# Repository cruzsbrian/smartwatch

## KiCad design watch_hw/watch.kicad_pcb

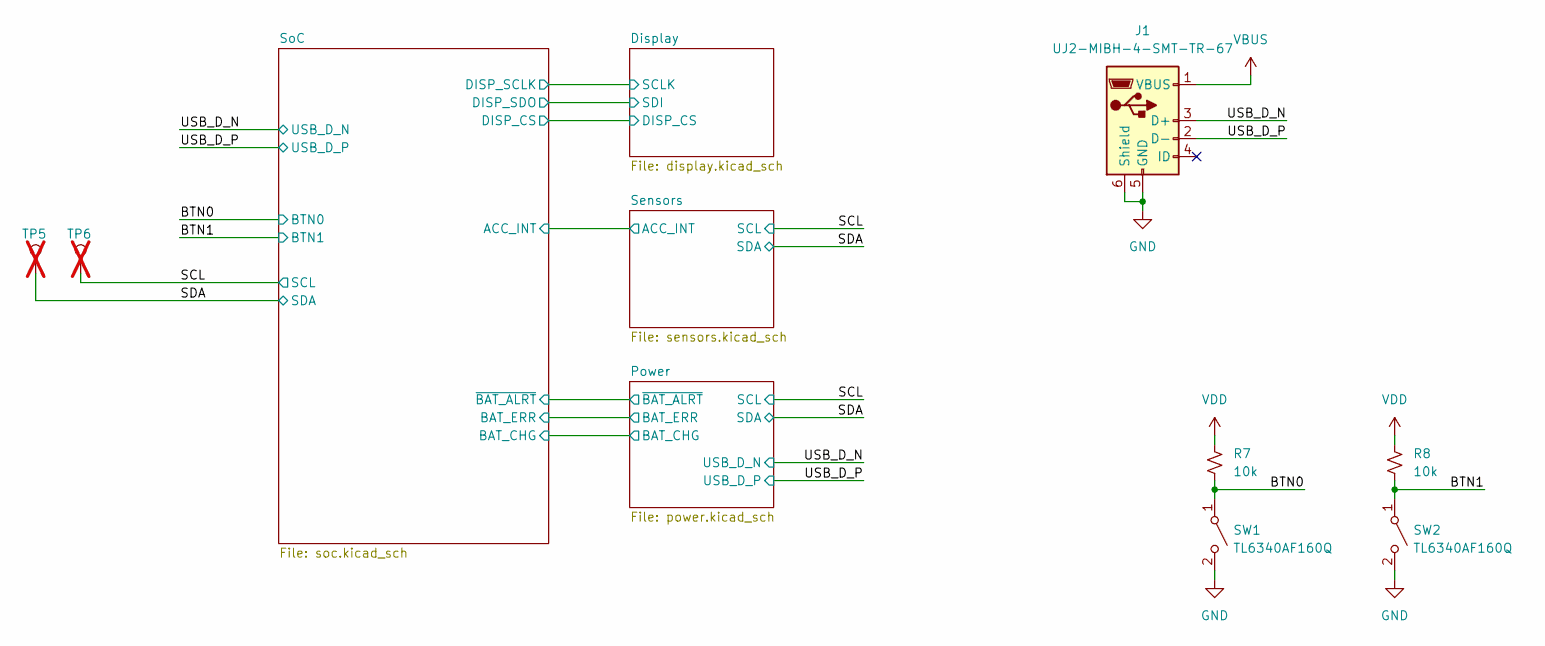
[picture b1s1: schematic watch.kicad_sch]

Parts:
J1: UJ2-MIBH-4-SMT-TR-67; Manufacturer Part Number UJ2-MIBH-4-SMT-TR-67; LCSC C22359766
R7, R8: 10k; R_0402_1005Metric_Pad0.72x0.64mm_HandSolder; Manufacturer Part Number 0402WGF1002TCE; LCSC C25744
SW1, SW2: TL6340AF160Q; SW_TL6340AF160Q; Manufacturer Part Number TL6340AF160Q; LCSC C4944967
TP5, TP6: TestPoint; TestPoint_Keystone_5015_Micro_Mini; not fitted

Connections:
/BTN0: R7.2, SW1.1 (A); also elsewhere on the board
/BTN1: R8.2, SW2.1 (A); also elsewhere on the board
/SCL: TP6.1; also elsewhere on the board
/SDA: TP5.1; also elsewhere on the board
/USB_D_N: J1.3 (D+); also elsewhere on the board
/USB_D_P: J1.2 (D-); also elsewhere on the board
GND: J1.5 (GND), J1.6 (Shield), SW1.2 (B), SW2.2 (B); also elsewhere on the board
VBUS: J1.1 (VBUS); also elsewhere on the board
VDD: R7.1, R8.1; also elsewhere on the board

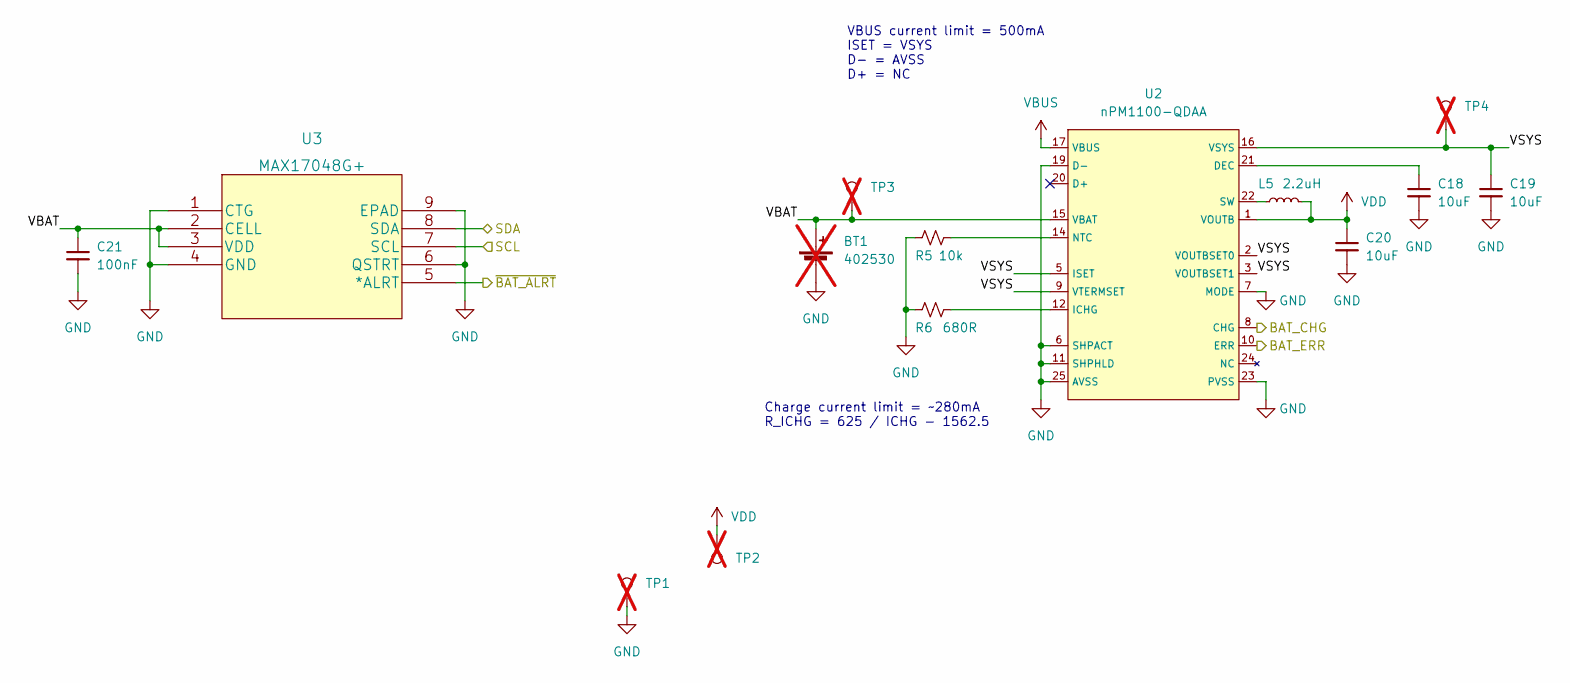
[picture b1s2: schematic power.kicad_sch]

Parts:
BT1: 402530; PinHeader_1x02_P1.27mm_Vertical; not fitted
C18, C19, C20: 10uF; C_0805_2012Metric_Pad1.18x1.45mm_HandSolder; Manufacturer Part Number CL21A106KAYNNNE; LCSC C15850
C21: 100nF; C_0402_1005Metric_Pad0.74x0.62mm_HandSolder; Manufacturer Part Number CL05B104KO5NNNC; LCSC C1525
L5: 2.2uH; L_0805_2012Metric_Pad1.05x1.20mm_HandSolder; Manufacturer Part Number LQM21PN2R2MGHL; LCSC C341781
R5: 10k; R_0402_1005Metric_Pad0.72x0.64mm_HandSolder; Manufacturer Part Number 0402WGF1002TCE; LCSC C25744
R6: 680R; R_0402_1005Metric_Pad0.72x0.64mm_HandSolder; Manufacturer Part Number 0402WGF6800TCE; LCSC C25130
TP1, TP2, TP3, TP4: TestPoint; TestPoint_Keystone_5015_Micro_Mini; not fitted
U2: nPM1100-QDAA; QFN-24-1EP_4x4mm_P0.5mm_EP2.15x2.15mm; Manufacturer Part Number NPM1100-QDAA-R; LCSC C5816773
U3: MAX17048G+; MAX17048G&plus_; Manufacturer Part Number MAX17048G+T10; LCSC C2682616

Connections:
/Power/BAT_CHG: U2.8 (CHG); also elsewhere on the board
/Power/BAT_ERR: U2.10 (ERR); also elsewhere on the board
/Power/VBAT: BT1.1 (+), C21.1, TP3.1, U2.15 (VBAT), U3.2 (CELL), U3.3 (VDD)
/Power/VSYS: C19.1, TP4.1, U2.2 (VOUTBSET0), U2.3 (VOUTBSET1), U2.5 (ISET), U2.9 (VTERMSET), U2.16 (VSYS)
/Power/~BAT_ALRT: U3.5 (*ALRT); also elsewhere on the board
/SCL: U3.7 (SCL); also elsewhere on the board
/SDA: U3.8 (SDA); also elsewhere on the board
GND: BT1.2 (-), C18.2, C19.2, C20.2, C21.2, R5.1, R6.1, TP1.1, U2.6 (SHPACT), U2.7 (MODE), U2.11 (SHPHLD), U2.19 (D-), U2.23 (PVSS), U2.25 (AVSS), U3.1 (CTG), U3.4 (GND), U3.6 (QSTRT), U3.9 (EPAD); also elsewhere on the board
unnamed: C18.1, U2.21 (DEC)
unnamed: R6.2, U2.12 (ICHG)
unnamed: R5.2, U2.14 (NTC)
unnamed: L5.1, U2.22 (SW)
VBUS: U2.17 (VBUS); also elsewhere on the board
VDD: C20.1, L5.2, TP2.1, U2.1 (VOUTB); also elsewhere on the board

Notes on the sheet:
Charge current limit = ~280mA R_ICHG = 625 / ICHG - 1562.5
VBUS current limit = 500mA ISET = VSYS D- = AVSS D+ = NC

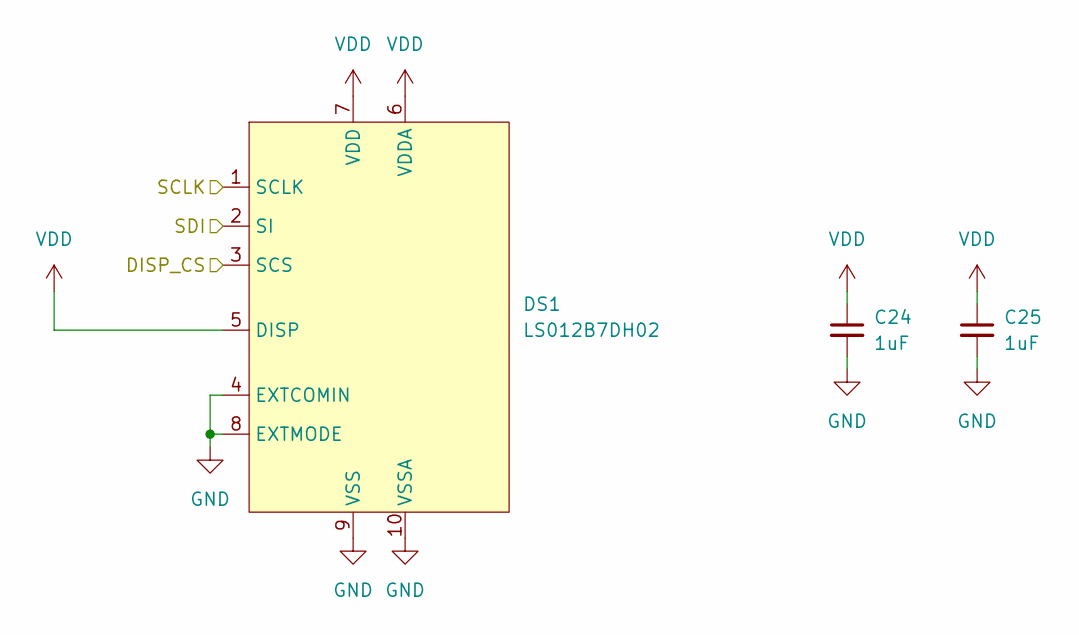
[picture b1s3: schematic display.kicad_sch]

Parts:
C24, C25: 1uF; C_0402_1005Metric_Pad0.74x0.62mm_HandSolder; Manufacturer Part Number CL05A105KA5NQNC; LCSC C52923
DS1: LS012B7DH02; AYF531035A; Manufacturer Part Number AYF531035A

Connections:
/Display/DISP_CS: DS1.3 (SCS); also elsewhere on the board
/Display/SCLK: DS1.1 (SCLK); also elsewhere on the board
/Display/SDI: DS1.2 (SI); also elsewhere on the board
GND: C24.2, C25.2, DS1.4 (EXTCOMIN), DS1.8 (EXTMODE), DS1.9 (VSS), DS1.10 (VSSA); also elsewhere on the board
VDD: C24.1, C25.1, DS1.5 (DISP), DS1.6 (VDDA), DS1.7 (VDD); also elsewhere on the board

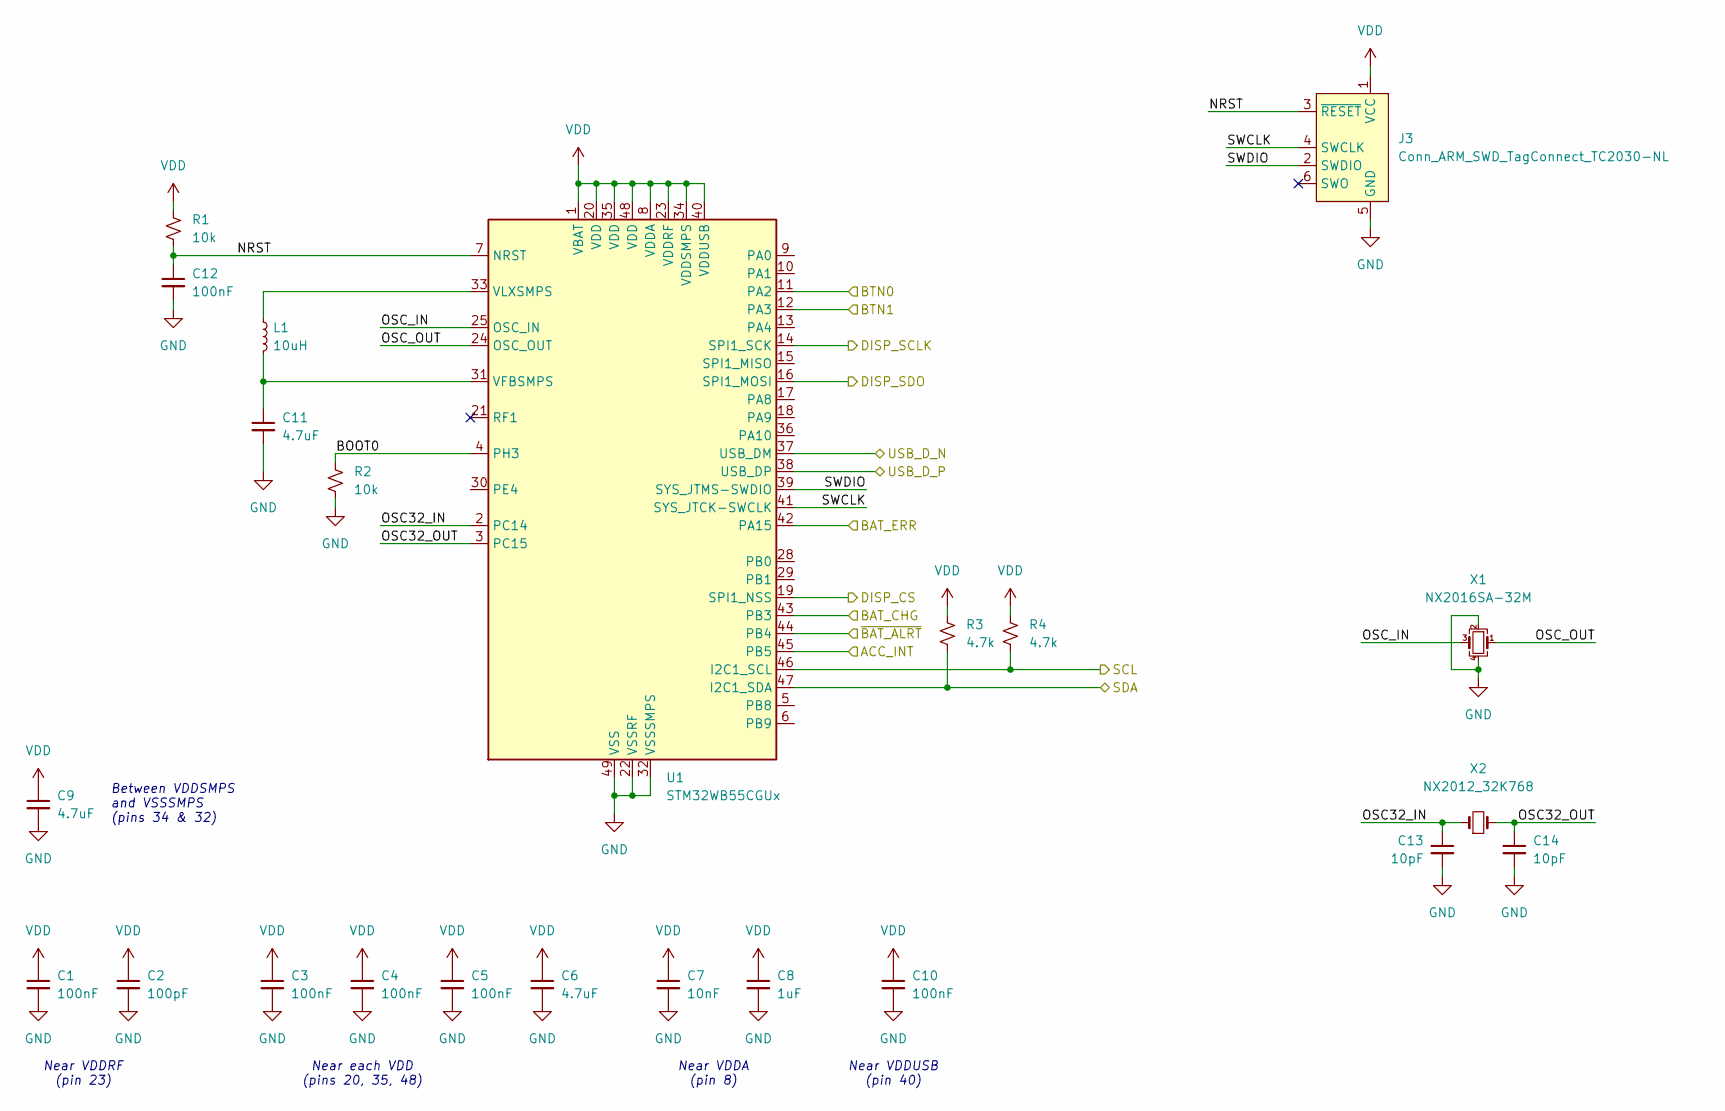
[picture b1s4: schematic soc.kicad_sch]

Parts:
C1, C3, C4, C5, C10, C12: 100nF; C_0402_1005Metric_Pad0.74x0.62mm_HandSolder; Manufacturer Part Number CL05B104KO5NNNC; LCSC C1525
C2: 100pF; C_0402_1005Metric_Pad0.74x0.62mm_HandSolder; Manufacturer Part Number CL05C101JB5NNNC; LCSC C26409
C6: 4.7uF; C_0402_1005Metric_Pad0.74x0.62mm_HandSolder; Manufacturer Part Number CL05A475MP5NRNC; LCSC C23733
C7: 10nF; C_0402_1005Metric_Pad0.74x0.62mm_HandSolder; Manufacturer Part Number CL05B103KB5NNNC; LCSC C15195
C8: 1uF; C_0402_1005Metric_Pad0.74x0.62mm_HandSolder; Manufacturer Part Number CL05A105KA5NQNC; LCSC C52923
C9, C11: 4.7uF; C_0603_1608Metric_Pad1.08x0.95mm_HandSolder; Manufacturer Part Number CL10A475KO8NNNC; LCSC C19666
C13, C14: 10pF; C_0402_1005Metric_Pad0.74x0.62mm_HandSolder; Manufacturer Part Number CL05C100JB5NNNC; LCSC C32949
J3: Conn_ARM_SWD_TagConnect_TC2030-NL; Tag-Connect_TC2030-IDC-NL_2x03_P1.27mm_Vertical
L1: 10uH; L_0805_2012Metric_Pad1.05x1.20mm_HandSolder; Manufacturer Part Number LQM21FN100M80L; LCSC C162582
R1, R2: 10k; R_0402_1005Metric_Pad0.72x0.64mm_HandSolder; Manufacturer Part Number 0402WGF1002TCE; LCSC C25744
R3, R4: 4.7k; R_0402_1005Metric_Pad0.72x0.64mm_HandSolder; Manufacturer Part Number 0402WGF4701TCE; LCSC C25900
U1: STM32WB55CGUx; QFN-48-1EP_7x7mm_P0.5mm_EP3.5x3.5mm; Manufacturer Part Number STM32WB55CGU6; LCSC C404023
X1: NX2016SA-32M; Crystal_SMD_2016-4Pin_2.0x1.6mm; Manufacturer Part Number NX2016SA-32MHZ-STD-CZS-5; LCSC C843260
X2: NX2012_32K768; Crystal_SMD_2012-2Pin_2.0x1.2mm_HandSoldering; Manufacturer Part Number NX2012SA-32.768KHZ-STD-MUB-2; LCSC C891748

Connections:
/BTN0: U1.11 (PA2); also elsewhere on the board
/BTN1: U1.12 (PA3); also elsewhere on the board
/Display/DISP_CS: U1.19 (SPI1_NSS); also elsewhere on the board
/Display/SCLK: U1.14 (SPI1_SCK); also elsewhere on the board
/Display/SDI: U1.16 (SPI1_MOSI); also elsewhere on the board
/Power/BAT_CHG: U1.43 (PB3); also elsewhere on the board
/Power/BAT_ERR: U1.42 (PA15); also elsewhere on the board
/Power/~BAT_ALRT: U1.44 (PB4); also elsewhere on the board
/SCL: R4.2, U1.46 (I2C1_SCL); also elsewhere on the board
/SDA: R3.2, U1.47 (I2C1_SDA); also elsewhere on the board
/Sensors/ACC_INT: U1.45 (PB5); also elsewhere on the board
/SoC/BOOT0: R2.1, U1.4 (PH3)
/SoC/NRST: C12.1, J3.3 (~RESET), R1.2, U1.7 (NRST)
/SoC/OSC32_IN: C13.1, U1.2 (PC14), X2.1
/SoC/OSC32_OUT: C14.1, U1.3 (PC15), X2.2
/SoC/OSC_IN: U1.25 (OSC_IN), X1.3
/SoC/OSC_OUT: U1.24 (OSC_OUT), X1.1
/SoC/SWCLK: J3.4 (SWCLK), U1.41 (SYS_JTCK-SWCLK)
/SoC/SWDIO: J3.2 (SWDIO), U1.39 (SYS_JTMS-SWDIO)
/USB_D_N: U1.37 (USB_DM); also elsewhere on the board
/USB_D_P: U1.38 (USB_DP); also elsewhere on the board
GND: C1.2, C2.2, C3.2, C4.2, C5.2, C6.2, C7.2, C8.2, C9.2, C10.2, C11.2, C12.2, C13.2, C14.2, J3.5 (GND), R2.2, U1.22 (VSSRF), U1.32 (VSSSMPS), U1.49 (VSS), X1.2, X1.4; also elsewhere on the board
unnamed: C11.1, L1.2, U1.31 (VFBSMPS)
unnamed: L1.1, U1.33 (VLXSMPS)
VDD: C1.1, C2.1, C3.1, C4.1, C5.1, C6.1, C7.1, C8.1, C9.1, C10.1, J3.1 (VCC), R1.1, R3.1, R4.1, U1.1 (VBAT), U1.8 (VDDA), U1.20 (VDD), U1.23 (VDDRF), U1.34 (VDDSMPS), U1.35 (VDD), U1.40 (VDDUSB), U1.48 (VDD); also elsewhere on the board

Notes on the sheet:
Near VDDUSB (pin 40)
Between VDDSMPS and VSSSMPS (pins 34 & 32)
Near VDDA (pin 8)
Near each VDD (pins 20, 35, 48)
Near VDDRF (pin 23)

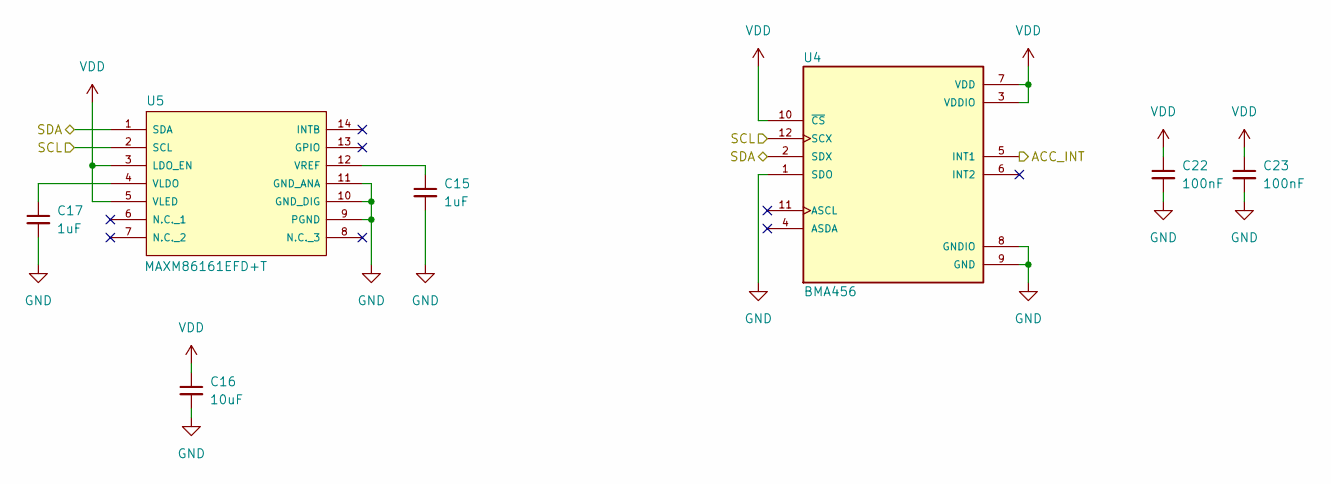
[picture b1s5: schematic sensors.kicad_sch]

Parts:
C15, C17: 1uF; C_0402_1005Metric_Pad0.74x0.62mm_HandSolder; Manufacturer Part Number CL05A105KA5NQNC; LCSC C52923
C16: 10uF; C_0805_2012Metric_Pad1.18x1.45mm_HandSolder; Manufacturer Part Number CL21A106KAYNNNE; LCSC C15850
C22, C23: 100nF; C_0402_1005Metric_Pad0.74x0.62mm_HandSolder; Manufacturer Part Number CL05B104KO5NNNC; LCSC C1525
U4: BMA456; XDCR_BMA456; PARTREV 2.0; LCSC C189518
U5: MAXM86161EFD+T; MAXM86161EFDT; Manufacturer Part Number MAXM86161EFD+T; LCSC C3178309

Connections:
/SCL: U4.12 (SCX), U5.2 (SCL); also elsewhere on the board
/SDA: U4.2 (SDX), U5.1 (SDA); also elsewhere on the board
/Sensors/ACC_INT: U4.5 (INT1); also elsewhere on the board
GND: C15.2, C16.2, C17.2, C22.2, C23.2, U4.1 (SDO), U4.8 (GNDIO), U4.9 (GND), U5.9 (PGND), U5.10 (GND_DIG), U5.11 (GND_ANA); also elsewhere on the board
unnamed: C17.1, U5.4 (VLDO)
unnamed: C15.1, U5.12 (VREF)
VDD: C16.1, C22.1, C23.1, U4.3 (VDDIO), U4.7 (VDD), U4.10 (~CS), U5.3 (LDO_EN), U5.5 (VLED); also elsewhere on the board

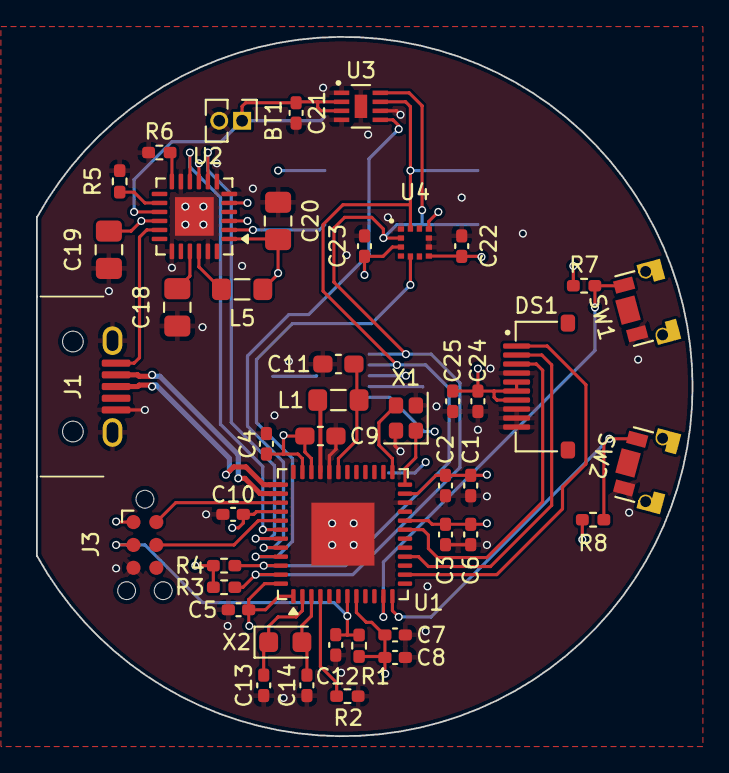
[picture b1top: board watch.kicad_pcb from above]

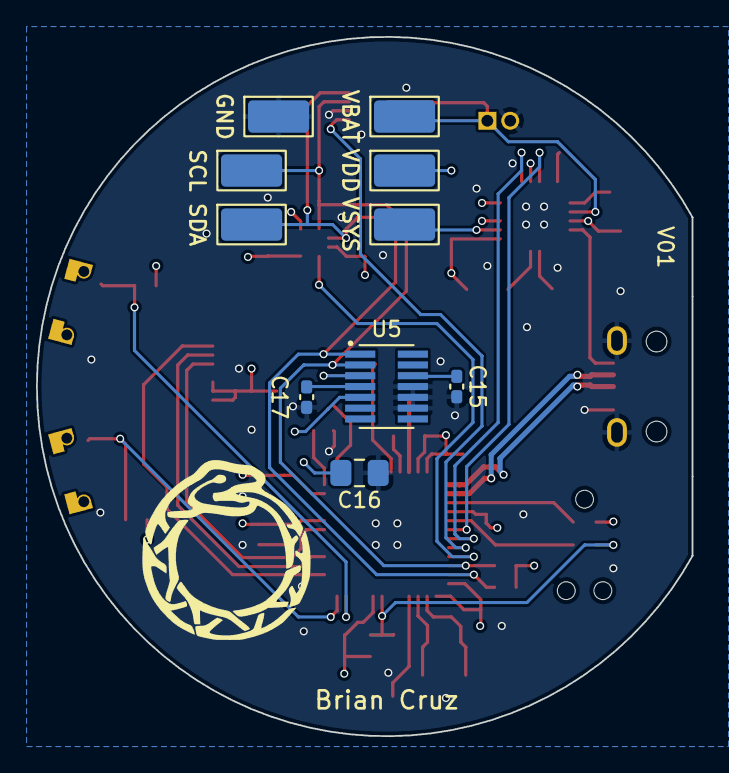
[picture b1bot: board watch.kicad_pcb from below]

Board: 6 copper layers, 36.4 x 38.8 mm, 55 parts (10 on the bottom side), 34 nets.

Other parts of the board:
DISP: LS012B7DH02

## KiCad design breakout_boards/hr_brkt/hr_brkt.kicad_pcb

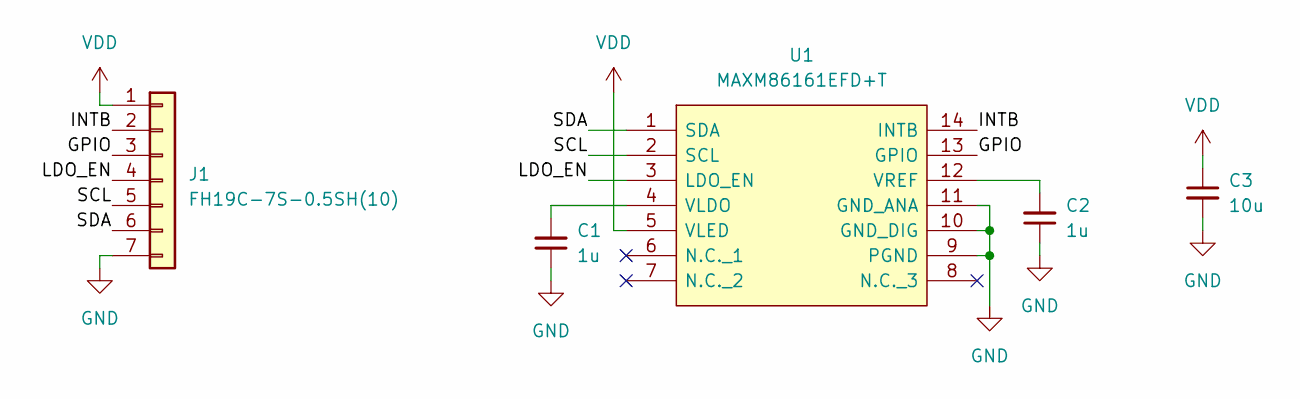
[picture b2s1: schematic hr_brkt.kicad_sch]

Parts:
C1, C2: 1u; C_0402_1005Metric_Pad0.74x0.62mm_HandSolder
C3: 10u; C_0402_1005Metric_Pad0.74x0.62mm_HandSolder
J1: FH19C-7S-0.5SH(10); FH19C_FPC
U1: MAXM86161EFD+T; MAXM86161EFDT; Mouser Part Number 700-MAXM86161EFD+T

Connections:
/GPIO: J1.3, U1.13 (GPIO)
/INTB: J1.2, U1.14 (INTB)
/LDO_EN: J1.4, U1.3 (LDO_EN)
/SCL: J1.5, U1.2 (SCL)
/SDA: J1.6, U1.1 (SDA)
GND: C1.1, C2.1, C3.2, J1.7, U1.9 (PGND), U1.10 (GND_DIG), U1.11 (GND_ANA)
unnamed: C1.2, U1.4 (VLDO)
unnamed: C2.2, U1.12 (VREF)
VDD: C3.1, J1.1, U1.5 (VLED)

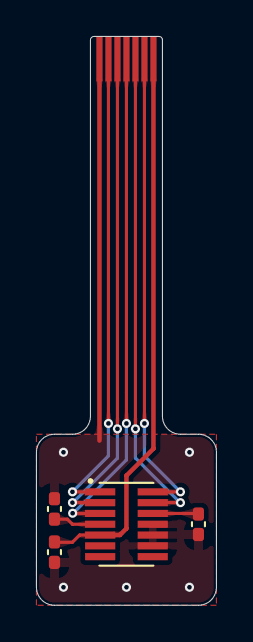
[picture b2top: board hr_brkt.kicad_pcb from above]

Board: 2 copper layers, 10.0 x 31.6 mm, 5 parts (0 on the bottom side), 9 nets.

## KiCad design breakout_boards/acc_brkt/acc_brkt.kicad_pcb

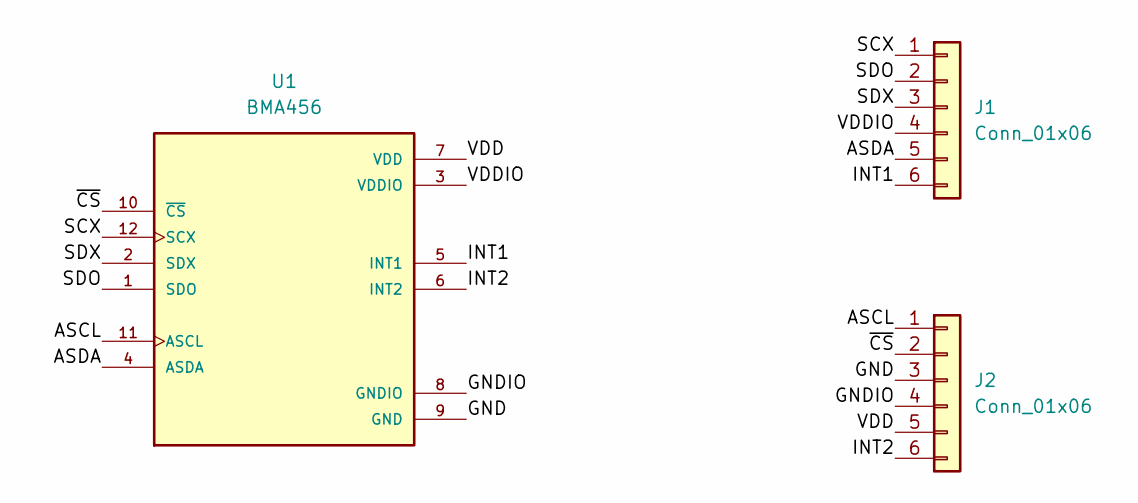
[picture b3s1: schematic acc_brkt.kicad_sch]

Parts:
J1, J2: Conn_01x06; PinHeader_1x06_P2.54mm_Vertical
U1: BMA456; XDCR_BMA456; PARTREV 2.0

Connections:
/ASCL: J2.1, U1.11 (ASCL)
/ASDA: J1.5, U1.4 (ASDA)
/GND: J2.3, U1.9 (GND)
/GNDIO: J2.4, U1.8 (GNDIO)
/INT1: J1.6, U1.5 (INT1)
/INT2: J2.6, U1.6 (INT2)
/SCX: J1.1, U1.12 (SCX)
/SDO: J1.2, U1.1 (SDO)
/SDX: J1.3, U1.2 (SDX)
/VDD: J2.5, U1.7 (VDD)
/VDDIO: J1.4, U1.3 (VDDIO)
/~CS: J2.2, U1.10 (~CS)

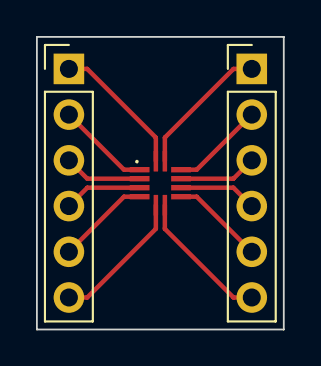
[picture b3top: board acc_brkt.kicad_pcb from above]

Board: 2 copper layers, 13.7 x 16.3 mm, 3 parts (0 on the bottom side), 12 nets.

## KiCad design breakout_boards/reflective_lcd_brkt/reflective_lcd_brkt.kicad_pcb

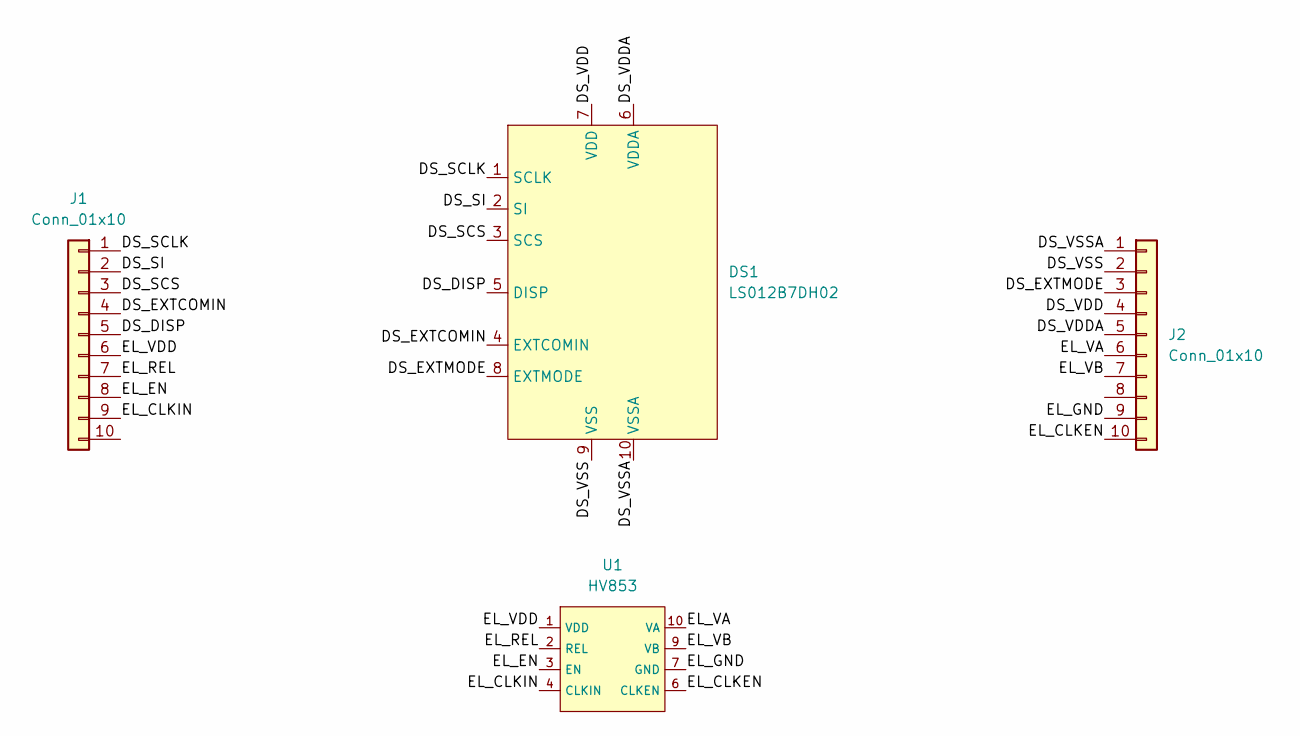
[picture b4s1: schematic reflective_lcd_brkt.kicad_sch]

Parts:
DS1: LS012B7DH02; AYF531035A
J1: Conn_01x10
J2: Conn_01x10; PinHeader_1x10_P2.54mm_Vertical
U1: HV853; DFN-10-1EP_3x3mm_P0.5mm_EP1.65x2.38mm

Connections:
/DS_DISP: DS1.5 (DISP), J1.5
/DS_EXTCOMIN: DS1.4 (EXTCOMIN), J1.4
/DS_EXTMODE: DS1.8 (EXTMODE), J2.3
/DS_SCLK: DS1.1 (SCLK), J1.1
/DS_SCS: DS1.3 (SCS), J1.3
/DS_SI: DS1.2 (SI), J1.2
/DS_VDD: DS1.7 (VDD), J2.4
/DS_VDDA: DS1.6 (VDDA), J2.5
/DS_VSS: DS1.9 (VSS), J2.2
/DS_VSSA: DS1.10 (VSSA), J2.1
/EL_CLKEN: J2.10, U1.6 (CLKEN)
/EL_CLKIN: J1.9, U1.4 (CLKIN)
/EL_EN: J1.8, U1.3 (EN)
/EL_REL: J1.7, U1.2 (REL)
/EL_VA: J2.6, U1.10 (VA)
/EL_VB: J2.7, U1.9 (VB)
/EL_VDD: J1.6, U1.1 (VDD)
GND: J2.8, J2.9, U1.7 (GND), U1.8 (GND)

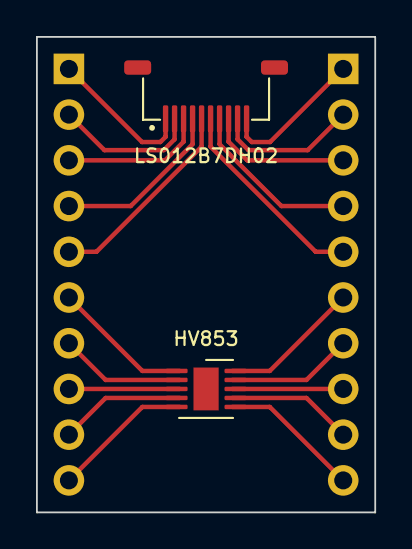
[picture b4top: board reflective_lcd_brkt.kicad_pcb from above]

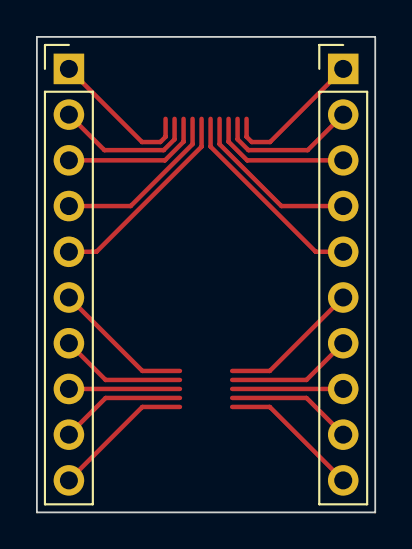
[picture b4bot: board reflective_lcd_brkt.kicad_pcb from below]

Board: 2 copper layers, 18.8 x 26.4 mm, 4 parts (2 on the bottom side), 18 nets.

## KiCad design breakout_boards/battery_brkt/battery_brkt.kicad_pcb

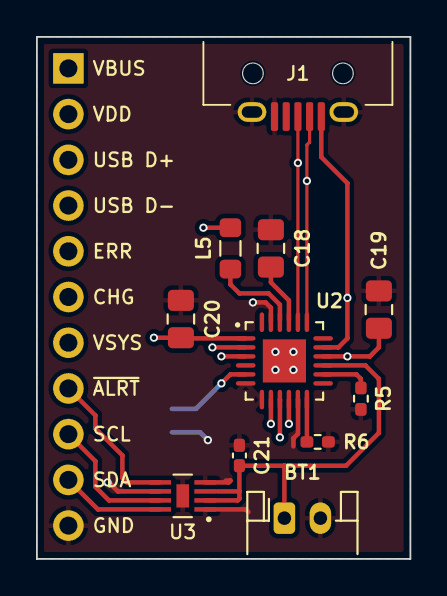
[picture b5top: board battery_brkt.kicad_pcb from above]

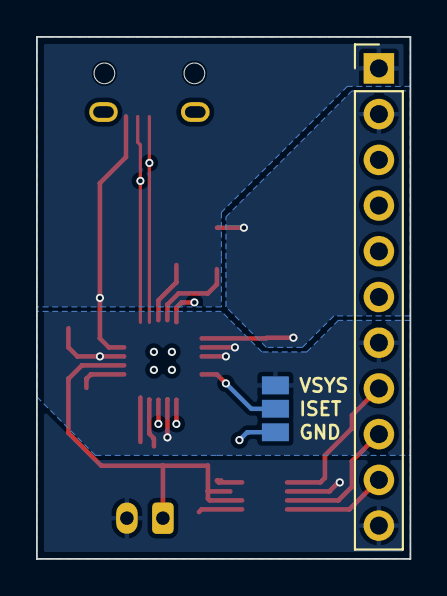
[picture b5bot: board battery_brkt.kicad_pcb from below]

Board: 4 copper layers, 20.8 x 29.0 mm, 13 parts (2 on the bottom side), 17 nets.

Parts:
BT1: 402530; JST_PH_S2B-PH-K_1x02_P2.00mm_Horizontal
C18, C19, C20: 10uF; C_0805_2012Metric_Pad1.18x1.45mm_HandSolder
C21: 0.1uF; C_0402_1005Metric_Pad0.74x0.62mm_HandSolder
J1: USB_B_Micro; UJ2-MIBH-4-SMT-TR-67
J2: Conn_01x11; PinHeader_1x11_P2.54mm_Vertical
JP1: SolderJumper_3_Open; SolderJumper-3_P1.3mm_Open_Pad1.0x1.5mm
L5: 2.2uH; L_0805_2012Metric_Pad1.05x1.20mm_HandSolder
R5: 10k; R_0402_1005Metric_Pad0.72x0.64mm_HandSolder
R6: 560R; R_0402_1005Metric_Pad0.72x0.64mm_HandSolder
U2: nPM1100-QD
U3: MAX17048G+; MAX17048G&plus_

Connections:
/BAT_CHG: J2.6, U2.8 (CHG)
/BAT_ERR: J2.5, U2.10 (ERR)
/ISET: JP1.2 (C), U2.5 (ISET)
/SCL: J2.9, U3.7 (SCL)
/SDA: J2.10, U3.8 (SDA)
/USB_D_N: J1.2 (D-), J2.4, U2.19 (D-)
/USB_D_P: J1.3 (D+), J2.3, U2.20 (D+)
/VBAT: BT1.1 (+), C21.1, U2.15 (VBAT), U3.2 (CELL), U3.3 (VDD)
/VSYS: C19.1, J2.7, JP1.1 (A), U2.2 (VOUTBSET0), U2.3 (VOUTBSET1), U2.9 (VTERMSET), U2.16 (VSYS)
/~BAT_ALRT: J2.8, U3.5 (*ALRT)
GND: BT1.2 (-), C18.2, C19.2, C20.2, C21.2, J1.5 (GND), J1.6 (Shield), J2.11, JP1.3 (B), R5.1, R6.1, U2.6 (SHPACT), U2.7 (MODE), U2.11 (SHPHLD), U2.23 (PVSS), U2.PAD, U3.1 (CTG), U3.4 (GND), U3.6 (QSTRT), U3.9 (EPAD)
unnamed: C18.1, U2.21 (DEC)
unnamed: R6.2, U2.12 (ICHG)
unnamed: R5.2, U2.14 (NTC)
unnamed: L5.1, U2.22 (SW)
VBUS: J1.1 (VBUS), J2.1, U2.17 (VBUS)
VDD: C20.1, J2.2, L5.2, U2.1 (VOUTB)

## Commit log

2023-09-26 Finalize (?) part selection, start layout
2023-10-08 Routing progress
2024-07-22 Clean up library symbols, update to kicad 8
2024-07-24 Add breakout boards, exclude gerbers from git
2024-07-24 SCH: add STM32 and most passives
2025-09-20 Start watch v1 layout
2026-01-06 Add pulse sensor straight to board, fix NPM1100 symbol/footprint
2026-01-06 Route usb data
2026-01-11 route a bunch, update USB plug board edge
2026-01-11 route a bunch more
2026-01-12 finish routing, need to fix DRC
2026-01-13 pass DRC
2026-01-13 fix 3D models
2026-01-13 move tagconnect slightly
2026-01-29 Add manufacturer/PN fields, select LCSC parts
2026-01-29 Slightly increase silkscreen text size
2026-01-29 Add ouroboros art
2026-01-29 Finish adding MPN info
2026-02-01 Expand via size for JLC
